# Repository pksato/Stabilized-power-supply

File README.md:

# Stabilized-power-supply
This power supply is orignal from https://www.electronics-lab.com/project/0-30-vdc-stabilized-power-supply-with-current-control-0-002-3-a/

EDA used is the Eagle 7.6

Sorry for lack of more details about this power supply.

Bridge Retifier and Main filter are not on these schematics.

Extra circuits are on this repository: https://github.com/pksato/TL431-Circuits

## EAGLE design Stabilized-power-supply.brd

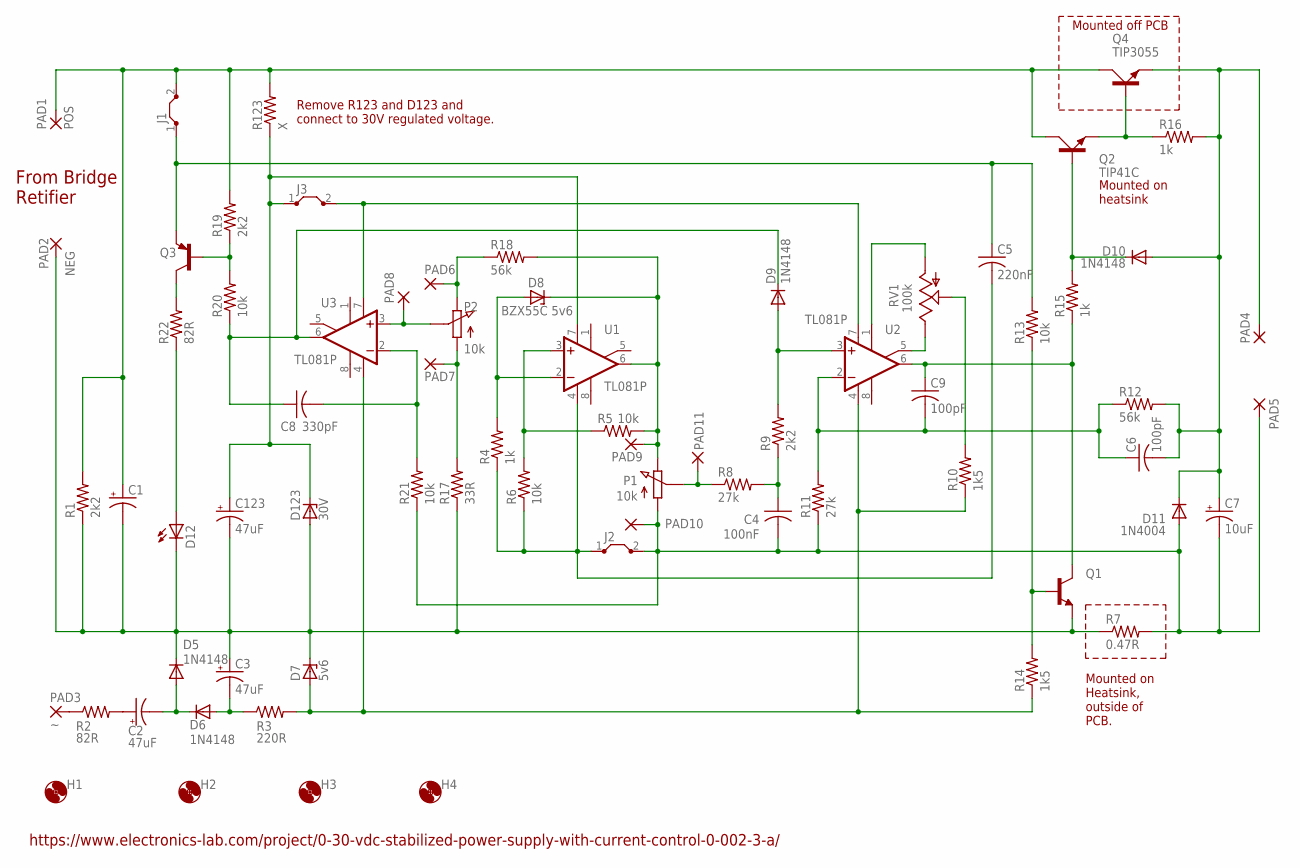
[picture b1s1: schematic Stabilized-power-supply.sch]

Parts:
C1: CPOL-USE5-10.5; E5-10,5
C2, C3, C123: 47uF; E2,5-7
C4: 100nF; C075-032X103
C5: 220nF; C075-032X103
C6, C9: 100pF; C050-024X044
C7: 10uF; E2,5-7
C8: 330pF; C050-024X044
D5, D6, D9, D10: 1N4148; D-5
D7: 5v6; ZDIO-7.5
D8: BZX55C 5v6; ZDIO-7.5
D11: 1N4004; DO41-10
D12: LED5MM
D123: 30V; ZDIO-7.5
H1, H2, H3, H4: MOUNT-HOLE2.8; 2,8
J1, J2, J3: J7MM; 07
PAD1: POS; 3,81/1,4
PAD2: NEG; 3,81/1,4
PAD3: 3,81/1,4
PAD4, PAD5: 3,81/1,4
PAD6, PAD7, PAD8, PAD9, PAD10, PAD11: 2,15/1,0
Q1: -NPN-TO92-CBE; TO92-CBE
Q2: TIP41C; TO126AV
Q3: -PNP-TO92-CBE; TO92-CBE
Q4: TIP3055; TOP3AV
R1: 2k2; 0411/15
R2, R22: 82R; 0207/10
R3: 220R; 0207/10
R4, R15, R16: 1k; 0207/10
R5, R6, R13, R20, R21: 10k; 0207/10
R7: 0.47R; 0617/22
R8, R11: 27k; 0207/10
R9, R19: 2k2; 0207/10
R10, R14: 1k5; 0207/10
R12, R18: 56k; 0207/10
R17: 33R; 0207/10
R123: X; 0207/10
RV1: 100k; ECP10P
U1, U2, U3: TL081P; DIL08

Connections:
unnamed: Q3.C, R22.2
unnamed: C1.+, J1.2, PAD1.1, Q2.C, Q4.C, R1.2, R19.2, R123.2
unnamed: Q3.B, R19.1, R20.2
unnamed: C8.1, D9.C, R20.1, U3.6 (OUT)
unnamed: PAD8.1, U3.3 (+IN)
unnamed: PAD6.1, R18.1
unnamed: D12.A, R22.1
unnamed: C123.+, D123.C, J3.1, R123.1, U1.7 (V+)
unnamed: C1.-, C3.+, C123.-, D5.C, D7.C, D12.K (C), D123.A, PAD2.1, Q1.E, R1.1, R7.1, R17.1
unnamed: C6.2, C7.+, D10.A, D11.C, PAD4.1, Q4.E, R12.2, R16.2
unnamed: D7.A, R3.2, R10.1, R14.1, U2.4 (V-), U3.4 (V-)
unnamed: C8.2, R21.2, U3.2 (-IN)
unnamed: D8.A, R4.2, U1.2 (-IN)
unnamed: R5.1, R6.2, U1.3 (+IN)
unnamed: PAD7.1, R17.2
unnamed: C4.2, C7.-, D11.A, J2.2, PAD5.1, PAD10.1, R7.2, R11.1, R21.1
unnamed: Q1.B, R13.1, R14.2
unnamed: D8.C, PAD9.1, R5.2, R18.2, U1.6 (OUT)
unnamed: C5.1, J1.1, Q3.E, R13.2
unnamed: PAD11.1, R8.1
unnamed: C4.1, R8.2, R9.1
unnamed: D9.A, R9.2, U2.3 (+IN)
unnamed: C6.1, C9.2, R11.2, R12.1, U2.2 (-IN)
unnamed: D10.C, Q2.B, R15.2
unnamed: C9.1, Q1.C, R15.1, U2.6 (OUT)
unnamed: RV1.A, U2.1 (ON1)
unnamed: RV1.E, U2.5 (ON2)
unnamed: R10.2, RV1.S
unnamed: Q2.E, Q4.B, R16.1
unnamed: C3.-, D6.A, R3.1
unnamed: J3.2, U2.7 (V+), U3.7 (V+)
unnamed: C5.2, J2.1, R4.1, R6.1, U1.4 (V-)
unnamed: C2.-, D5.A, D6.C
unnamed: C2.+, R2.2
unnamed: PAD3.1, R2.1

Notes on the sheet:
https://www.electronics-lab.com/project/0-30-vdc-stabilized-power-supply-with-current-control-0-002-3-a/
From Bridge Retifier
Mounted off PCB
Mounted on heatsink
Mounted on Heatsink, outside of PCB.
Remove R123 and D123 and connect to 30V regulated voltage.

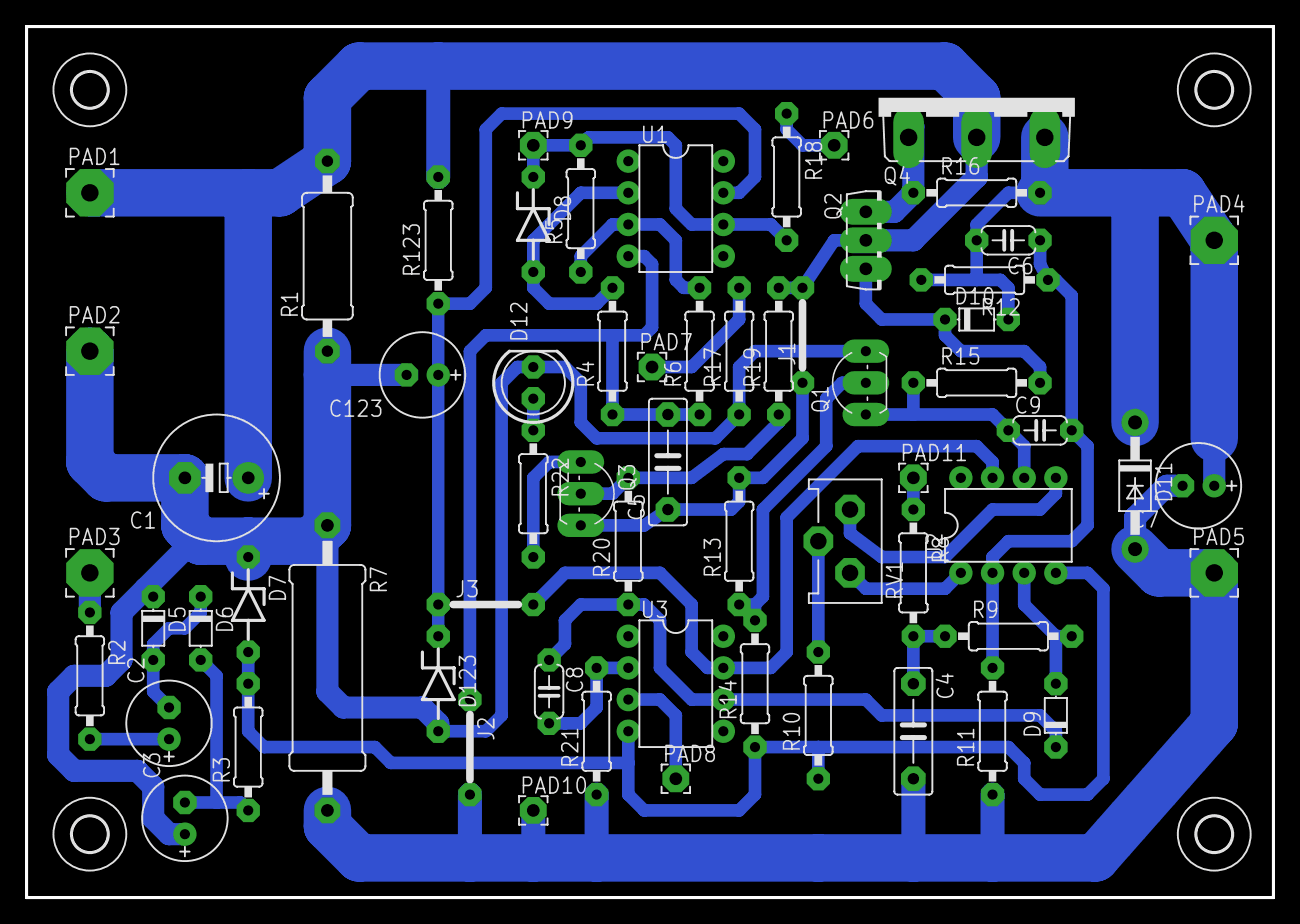
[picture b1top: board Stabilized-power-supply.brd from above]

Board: 2 copper layers, 100.0 x 69.8 mm, 68 parts (0 on the bottom side), 35 nets.
